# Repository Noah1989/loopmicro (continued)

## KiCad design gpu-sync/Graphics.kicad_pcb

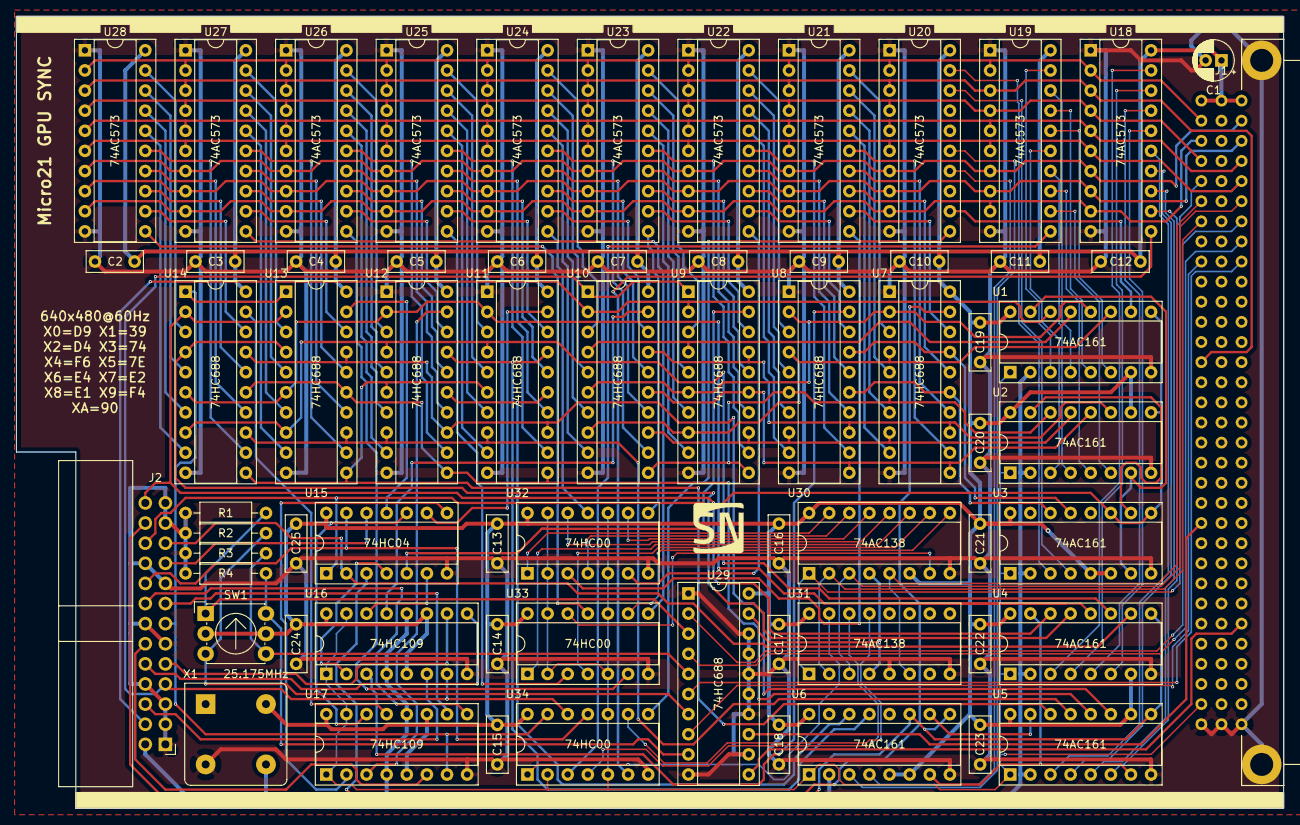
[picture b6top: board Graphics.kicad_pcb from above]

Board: 2 copper layers, 160.0 x 100.0 mm, 67 parts (0 on the bottom side), 183 nets.

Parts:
C1: CP_Small; CP_Radial_D5.0mm_P2.00mm
C2, C3, C4, C5, C6, C7, C8, C9, C10, C11, C12, C13, C14, C15, C16, C17, C18, C19, C20, C21, C22, C23, C24, C25: C_Small; C_Disc_D7.0mm_W2.5mm_P5.00mm
J1: C96ABC; Socket_DIN41612-CaseC1-full-Male-96Pin-3rows
J2: Conn_01x26_Male; IDC-Header_2x13_P2.54mm_Horizontal
R1, R2, R3, R4: 100k; R_Axial_DIN0207_L6.3mm_D2.5mm_P10.16mm_Horizontal
SW1: SW_Coded_SH-7050; Nidec_Copal_SH-7010C
U1, U2, U3, U4, U5, U6: 74AC161; DIP-16_W7.62mm_Socket
U7, U8, U9, U10, U11, U12, U13, U14, U29: 74HC688; DIP-20_W7.62mm_Socket
U15: 74HC04; DIP-14_W7.62mm_Socket
U16, U17: 74HC109; DIP-16_W7.62mm_Socket
U18, U19, U20, U21, U22, U23, U24, U25, U26, U27, U28: 74AC573; DIP-20_W7.62mm_Socket
U30, U31: 74AC138; DIP-16_W7.62mm_Socket
U32, U33, U34: 74HC00; DIP-14_W7.62mm_Socket
X1: 25.175MHz; Oscillator_DIP-8_LargePads

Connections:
/BLANK: J2.18, U15.13, U34.11
/Column Counter/CE: U1.10, U20.12
/Column Counter/D0: U1.3, U19.19
/Column Counter/D1: U1.4, U19.18
/Column Counter/D2: U1.5, U19.17
/Column Counter/D3: U1.6, U19.16
/Column Counter/D4: U2.3, U19.15
/Column Counter/D5: U2.4, U19.14
/Column Counter/D6: U2.5, U19.13
/Column Counter/D7: U2.6, U19.12
/Column Counter/D8: U3.3, U20.19
/Column Counter/D9: U3.4, U20.18
/HBLANK: J2.6, U16.6
/HBLANK Generator/P0: U1.12, U7.2, U8.2, U9.6, U10.6
/HBLANK Generator/P1: U1.11, U7.4, U8.4, U9.8, U10.8
/HBLANK Generator/P2: U2.14, U7.6, U8.6, U9.11, U10.11
/HBLANK Generator/P3: U2.13, U7.8, U8.8, U9.13, U10.13
/HBLANK Generator/P4: U2.12, U7.11, U8.11, U9.15, U10.15
/HBLANK Generator/P5: U2.11, U7.13, U8.13, U9.17, U10.17
/HBLANK Generator/P6: U3.14, U7.15, U8.15
/HBLANK Generator/P7: U3.13, U7.17, U8.17
/HSYNC: J2.9, U16.10
/HSYNC Generator/P0: J2.4, U1.14, U9.2, U10.2
/HSYNC Generator/P1: U1.13, U9.4, U10.4
/PCLK: J2.2, U1.2, U2.2, U3.2, U4.2, U5.2, U6.2, U16.4, U16.12, U17.4, U17.12, X1.5
/Row Counter/D0: U4.3, U18.19
/Row Counter/D1: U4.4, U18.18
/Row Counter/D2: U4.5, U18.17
/Row Counter/D3: U4.6, U18.16
/Row Counter/D4: U5.3, U18.15
/Row Counter/D5: U5.4, U18.14
/Row Counter/D6: U5.5, U18.13
/Row Counter/D7: U5.6, U18.12
/Row Counter/D8: U6.3, U20.15
/Row Counter/D9: U6.4, U20.14
/TCC: J2.21, U4.10, U15.2
/VBLANK: J2.12, U17.6
/VBLANK Generator/P0: U4.12, U11.2, U12.2, U13.6, U14.6
/VBLANK Generator/P1: U4.11, U11.4, U12.4, U13.8, U14.8
/VBLANK Generator/P2: U5.14, U11.6, U12.6, U13.11, U14.11
/VBLANK Generator/P3: U5.13, U11.8, U12.8, U13.13, U14.13
/VBLANK Generator/P4: U5.12, U11.11, U12.11, U13.15, U14.15
/VBLANK Generator/P5: U5.11, U11.13, U12.13, U13.17, U14.17
/VBLANK Generator/P6: U6.14, U11.15, U12.15
/VBLANK Generator/P7: U6.13, U11.17, U12.17
/VSYNC: J2.15, U17.10
/VSYNC Generator/P0: J2.26, U4.14, U13.2, U14.2
/VSYNC Generator/P1: U4.13, U13.4, U14.4
/~BLANK: J2.19, U15.12
/~HBLANK: J2.7, U9.1, U10.1, U16.7, U34.12
/~HSYNC: J2.10, U16.9
/~TCC: J2.22, U1.9, U2.9, U3.9, U3.11, U15.1
/~TCR: J2.24, U4.9, U5.9, U6.9, U6.11
/~VBLANK: J2.13, U13.1, U14.1, U17.7, U34.13
/~VSYNC: J2.16, U17.9
A0: J1.C5, U30.1, U31.1
A1: J1.C7, U30.2, U31.2
A2: J1.A6, U30.3, U31.3
A3: J1.C6, U30.5, U31.6
A4: J1.A7, U29.2
A5: J1.A8, U29.4
A6: J1.A9, U29.6
A7: J1.C9, U29.8
D0: J1.C2, U18.2, U19.2, U20.2, U21.2, U22.2, U23.2, U24.2, U25.2, U26.2, U27.2, U28.2
D1: J1.C14, U18.3, U19.3, U20.3, U21.3, U22.3, U23.3, U24.3, U25.3, U26.3, U27.3, U28.3
D2: J1.C4, U18.4, U19.4, U20.4, U21.4, U22.4, U23.4, U24.4, U25.4, U26.4, U27.4, U28.4
D3: J1.A4, U18.5, U19.5, U20.5, U21.5, U22.5, U23.5, U24.5, U25.5, U26.5, U27.5, U28.5
D4: J1.A5, U18.6, U19.6, U20.6, U21.6, U22.6, U23.6, U24.6, U25.6, U26.6, U27.6, U28.6
D5: J1.A2, U18.7, U19.7, U20.7, U21.7, U22.7, U23.7, U24.7, U25.7, U26.7, U27.7, U28.7
D6: J1.A3, U18.8, U19.8, U20.8, U21.8, U22.8, U23.8, U24.8, U25.8, U26.8, U27.8, U28.8
D7: J1.C3, U18.9, U19.9, U20.9, U21.9, U22.9, U23.9, U24.9, U25.9, U26.9, U27.9, U28.9
GND: C1.2, C2.1, C3.1, C4.1, C5.1, C6.1, C7.1, C8.1, C9.1, C10.1, C11.1, C12.1, C13.1, C14.1, C15.1, C16.1, C17.1, C18.1, C19.1, C20.1, C21.1, C22.1, C23.1, C24.1, C25.1, J1.A32, J1.B32, J1.C32, J2.1, J2.3, J2.5, J2.8, J2.11, J2.14, J2.17, J2.20, J2.23, J2.25, R1.2, R2.2, R3.2, R4.2, U1.8, U2.8, U3.8, U4.8, U5.8, U6.8, U7.1, U7.10, U8.1, U8.10, U9.10, U10.10, U11.1, U11.10, U12.1, U12.10, U13.10, U14.10, U15.7, U16.8, U17.8, U18.1, U18.10, U19.1, U19.10, U20.1, U20.10, U21.1, U21.10, U22.1, U22.10, U23.1, U23.10, U24.1, U24.10, U25.1, U25.10, U26.1, U26.10, U27.1, U27.10, U28.1, U28.10, U29.1, U29.10, U29.12, U29.14, U29.15, U29.16, U29.17, U29.18, U30.8, U31.5, U31.8, U32.7, U33.7, U34.7, X1.4
unnamed: R1.1, SW1.1, U29.3
unnamed: R2.1, SW1.4, U29.7
unnamed: R3.1, SW1.2, U29.5
unnamed: R4.1, SW1.8, U29.9
unnamed: U1.15, U2.7, U3.7
unnamed: U2.15, U3.10
unnamed: U4.15, U5.7, U6.7
unnamed: U5.15, U6.10
unnamed: U10.3, U24.19
unnamed: U10.5, U24.18
unnamed: U10.7, U24.17
unnamed: U10.9, U24.16
unnamed: U10.12, U24.15
unnamed: U10.14, U24.14
unnamed: U10.16, U24.13
unnamed: U10.18, U24.12
unnamed: U10.19, U16.13
unnamed: U11.3, U25.19
unnamed: U11.5, U25.18
unnamed: U11.7, U25.17
unnamed: U11.9, U25.16
unnamed: U11.12, U25.15
unnamed: U11.14, U25.14
unnamed: U11.16, U25.13
unnamed: U11.18, U25.12
unnamed: U11.19, U15.9
unnamed: U12.3, U26.19
unnamed: U12.5, U26.18
unnamed: U12.7, U26.17
unnamed: U12.9, U26.16
unnamed: U12.12, U26.15
unnamed: U12.14, U26.14
unnamed: U12.16, U26.13
unnamed: U12.18, U26.12
unnamed: U12.19, U17.3
unnamed: U13.3, U27.19
unnamed: U13.5, U27.18
unnamed: U13.7, U27.17
unnamed: U13.9, U27.16
unnamed: U13.12, U27.15
unnamed: U13.14, U27.14
unnamed: U13.16, U27.13
unnamed: U13.18, U27.12
unnamed: U13.19, U15.11
unnamed: U14.3, U28.19
unnamed: U14.5, U28.18
unnamed: U14.7, U28.17
unnamed: U14.9, U28.16
unnamed: U14.12, U28.15
unnamed: U14.14, U28.14
unnamed: U14.16, U28.13
unnamed: U14.18, U28.12
unnamed: U14.19, U17.13
unnamed: U7.19, U15.3
unnamed: U15.4, U16.2
unnamed: U9.19, U15.5
unnamed: U15.6, U16.14
unnamed: U15.8, U17.2
unnamed: U15.10, U17.14
unnamed: U8.19, U16.3
unnamed: U18.11, U34.6
unnamed: U19.11, U34.3
unnamed: U20.11, U34.8
unnamed: U21.11, U32.3
unnamed: U7.18, U21.12
unnamed: U7.16, U21.13
unnamed: U7.14, U21.14
unnamed: U7.12, U21.15
unnamed: U7.9, U21.16
unnamed: U7.7, U21.17
unnamed: U7.5, U21.18
unnamed: U7.3, U21.19
unnamed: U22.11, U32.6
unnamed: U8.18, U22.12
unnamed: U8.16, U22.13
unnamed: U8.14, U22.14
unnamed: U8.12, U22.15
unnamed: U8.9, U22.16
unnamed: U8.7, U22.17
unnamed: U8.5, U22.18
unnamed: U8.3, U22.19
unnamed: U23.11, U32.8
unnamed: U9.18, U23.12
unnamed: U9.16, U23.13
unnamed: U9.14, U23.14
unnamed: U9.12, U23.15
unnamed: U9.9, U23.16
unnamed: U9.7, U23.17
unnamed: U9.5, U23.18
unnamed: U9.3, U23.19
unnamed: U24.11, U32.11
unnamed: U25.11, U33.3
unnamed: U26.11, U33.6
unnamed: U27.11, U33.8
unnamed: U28.11, U33.11
unnamed: U29.19, U30.4, U31.4
VCC: C1.1, C2.2, C3.2, C4.2, C5.2, C6.2, C7.2, C8.2, C9.2, C10.2, C11.2, C12.2, C13.2, C14.2, C15.2, C16.2, C17.2, C18.2, C19.2, C20.2, C21.2, C22.2, C23.2, C24.2, C25.2, J1.A1, J1.B1, J1.C1, SW1.C, U1.7, U1.16, U2.10, U2.16, U3.5, U3.6, U3.16, U4.7, U4.16, U5.10, U5.16, U6.5, U6.6, U6.16, U7.20, U8.20, U9.20, U10.20, U11.20, U12.20, U13.20, U14.20, U15.14, U16.5, U16.11, U16.16, U17.5, U17.11, U17.16, U18.20, U19.20, U20.20, U21.20, U22.20, U23.20, U24.20, U25.20, U26.20, U27.20, U28.20, U29.20, U30.6, U30.16, U31.16, U32.14, U33.14, U34.14, X1.8
~CS0: U30.15, U32.1
~CS1: U30.14, U32.4
~CS2: U30.13, U32.9
~CS3: U30.12, U32.12
~CS4: U30.11, U33.1
~CS5: U30.10, U33.4
~CS6: U30.9, U33.9
~CS7: U30.7, U33.12
~CS8: U31.15, U34.1
~CS9: U31.14, U34.4
~CS10: U31.13, U34.9
~IORQ: J1.A27, U29.11
~RESET: J1.C31, U1.1, U2.1, U3.1, U4.1, U5.1, U6.1, U16.1, U16.15, U17.1, U17.15, U32.2, U32.5, U32.10, U32.13, U33.2, U33.5, U33.10, U33.13, U34.2, U34.5, U34.10
~WR: J1.C22, U29.13

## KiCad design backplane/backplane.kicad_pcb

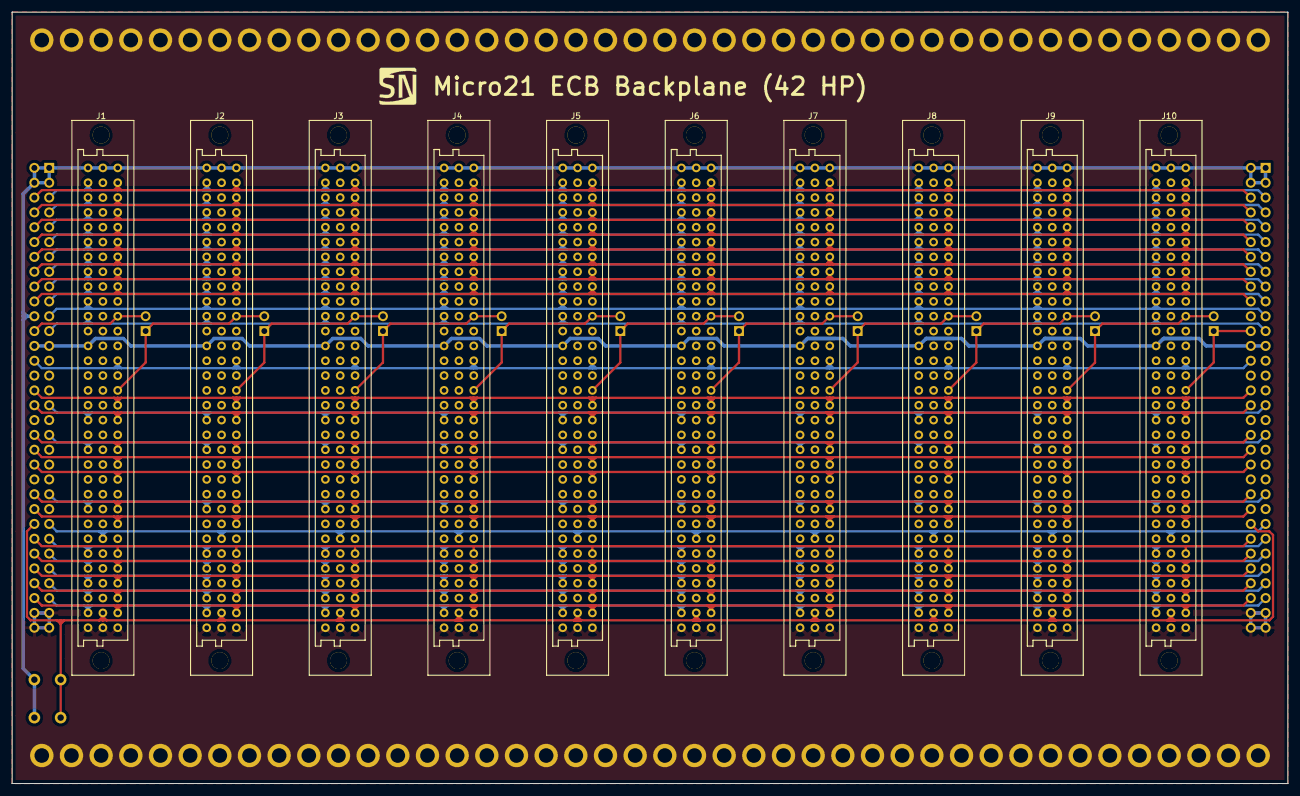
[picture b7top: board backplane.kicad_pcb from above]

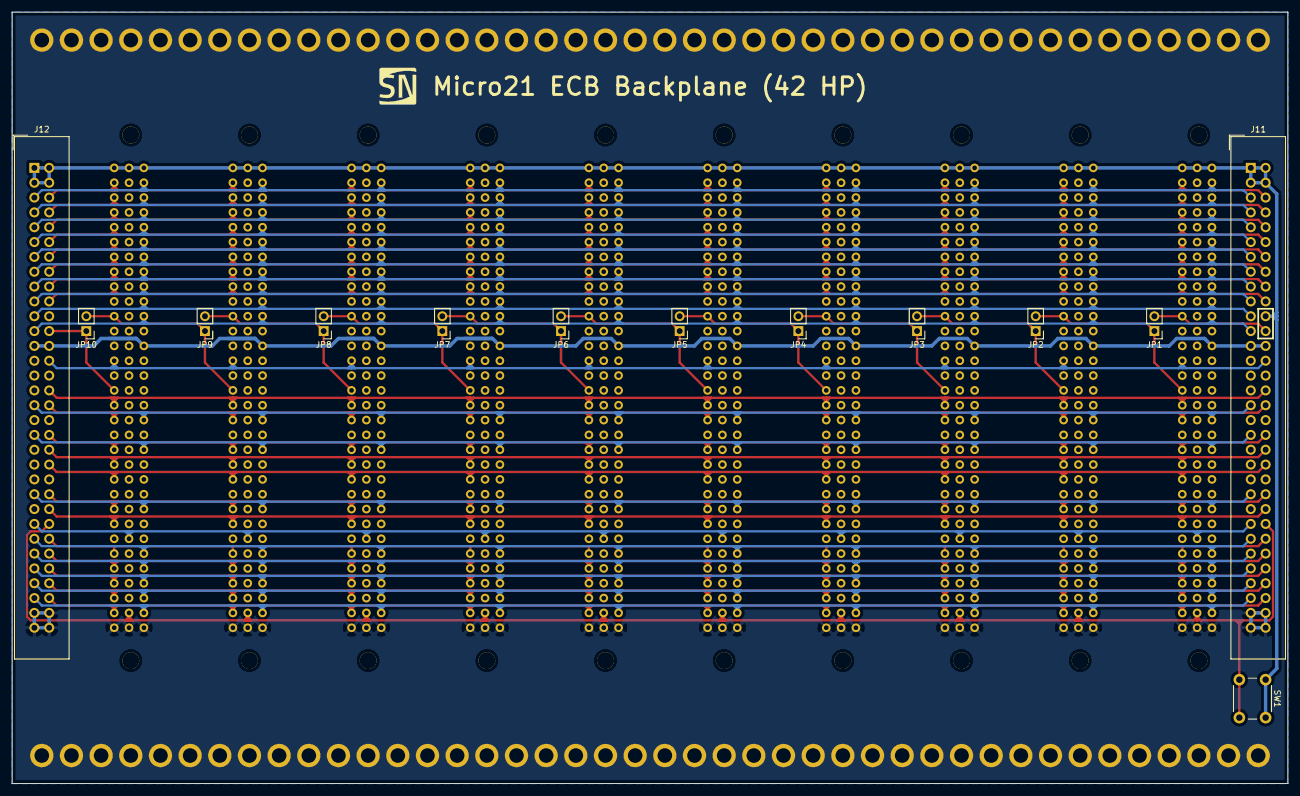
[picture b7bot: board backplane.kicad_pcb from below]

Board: 2 copper layers, 218.4 x 132.1 mm, 23 parts (13 on the bottom side), 55 nets.

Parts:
J1, J2, J3, J4, J5, J6, J7, J8, J9, J10: C96ABC; Socket_DIN41612-CaseC1-full-Female-96Pin-3rows
J11, J12: Conn_02x32_Odd_Even; IDC-Header_2x32_P2.54mm_Vertical
JP1, JP2, JP3, JP4, JP5, JP6, JP7, JP8, JP9, JP10: Jumper; PinHeader_1x02_P2.54mm_Vertical
SW1: SW_Push; SW_PUSH_6mm_H7.3mm

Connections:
+12V: J1.A13, J2.A13, J3.A13, J4.A13, J5.A13, J6.A13, J7.A13, J8.A13, J9.A13, J10.A13, J11.25, J11.26, J12.25, J12.26
+BATT: J1.A24, J2.A24, J3.A24, J4.A24, J5.A24, J6.A24, J7.A24, J8.A24, J9.A24, J10.A24, J11.45, J12.45
A0: J1.C5, J2.C5, J3.C5, J4.C5, J5.C5, J6.C5, J7.C5, J8.C5, J9.C5, J10.C5, J11.12, J12.12
A1: J1.C7, J2.C7, J3.C7, J4.C7, J5.C7, J6.C7, J7.C7, J8.C7, J9.C7, J10.C7, J11.16, J12.16
A2: J1.A6, J2.A6, J3.A6, J4.A6, J5.A6, J6.A6, J7.A6, J8.A6, J9.A6, J10.A6, J11.13, J12.13
A3: J1.C6, J2.C6, J3.C6, J4.C6, J5.C6, J6.C6, J7.C6, J8.C6, J9.C6, J10.C6, J11.14, J12.14
A4: J1.A7, J2.A7, J3.A7, J4.A7, J5.A7, J6.A7, J7.A7, J8.A7, J9.A7, J10.A7, J11.15, J12.15
A5: J1.A8, J2.A8, J3.A8, J4.A8, J5.A8, J6.A8, J7.A8, J8.A8, J9.A8, J10.A8, J11.17, J12.17
A6: J1.A9, J2.A9, J3.A9, J4.A9, J5.A9, J6.A9, J7.A9, J8.A9, J9.A9, J10.A9, J11.19, J12.19
A7: J1.C9, J2.C9, J3.C9, J4.C9, J5.C9, J6.C9, J7.C9, J8.C9, J9.C9, J10.C9, J11.20, J12.20
A8: J1.C8, J2.C8, J3.C8, J4.C8, J5.C8, J6.C8, J7.C8, J8.C8, J9.C8, J10.C8, J11.18, J12.18
A9: J1.A30, J2.A30, J3.A30, J4.A30, J5.A30, J6.A30, J7.A30, J8.A30, J9.A30, J10.A30, J11.57, J12.57
A10: J1.C18, J2.C18, J3.C18, J4.C18, J5.C18, J6.C18, J7.C18, J8.C18, J9.C18, J10.C18, J11.34, J12.34
A11: J1.C17, J2.C17, J3.C17, J4.C17, J5.C17, J6.C17, J7.C17, J8.C17, J9.C17, J10.C17, J11.32, J12.32
A12: J1.C27, J2.C27, J3.C27, J4.C27, J5.C27, J6.C27, J7.C27, J8.C27, J9.C27, J10.C27, J11.52, J12.52
A13: J1.A29, J2.A29, J3.A29, J4.A29, J5.A29, J6.A29, J7.A29, J8.A29, J9.A29, J10.A29, J11.55, J12.55
A14: J1.A18, J2.A18, J3.A18, J4.A18, J5.A18, J6.A18, J7.A18, J8.A18, J9.A18, J10.A18, J11.33, J12.33
A15: J1.C28, J2.C28, J3.C28, J4.C28, J5.C28, J6.C28, J7.C28, J8.C28, J9.C28, J10.C28, J11.54, J12.54
CLK: J1.C29, J2.C29, J3.C29, J4.C29, J5.C29, J6.C29, J7.C29, J8.C29, J9.C29, J10.C29, J11.56, J12.56
D0: J1.C2, J2.C2, J3.C2, J4.C2, J5.C2, J6.C2, J7.C2, J8.C2, J9.C2, J10.C2, J11.6, J12.6
D1: J1.C14, J2.C14, J3.C14, J4.C14, J5.C14, J6.C14, J7.C14, J8.C14, J9.C14, J10.C14, J11.28, J12.28
D2: J1.C4, J2.C4, J3.C4, J4.C4, J5.C4, J6.C4, J7.C4, J8.C4, J9.C4, J10.C4, J11.10, J12.10
D3: J1.A4, J2.A4, J3.A4, J4.A4, J5.A4, J6.A4, J7.A4, J8.A4, J9.A4, J10.A4, J11.9, J12.9
D4: J1.A5, J2.A5, J3.A5, J4.A5, J5.A5, J6.A5, J7.A5, J8.A5, J9.A5, J10.A5, J11.11, J12.11
D5: J1.A2, J2.A2, J3.A2, J4.A2, J5.A2, J6.A2, J7.A2, J8.A2, J9.A2, J10.A2, J11.5, J12.5
D6: J1.A3, J2.A3, J3.A3, J4.A3, J5.A3, J6.A3, J7.A3, J8.A3, J9.A3, J10.A3, J11.7, J12.7
D7: J1.C3, J2.C3, J3.C3, J4.C3, J5.C3, J6.C3, J7.C3, J8.C3, J9.C3, J10.C3, J11.8, J12.8
GND: J1.A32, J1.B32, J1.C32, J2.A32, J2.B32, J2.C32, J3.A32, J3.B32, J3.C32, J4.A32, J4.B32, J4.C32, J5.A32, J5.B32, J5.C32, J6.A32, J6.B32, J6.C32, J7.A32, J7.B32, J7.C32, J8.A32, J8.B32, J8.C32, J9.A32, J9.B32, J9.C32, J10.A32, J10.B32, J10.C32, J11.61, J11.62, J11.63, J11.64, J12.61, J12.62, J12.63, J12.64
unnamed: J1.C11, J11.24, JP1.2
unnamed: J1.C16, J2.C11, JP1.1, JP2.2
unnamed: J2.C16, J3.C11, JP2.1, JP3.2
unnamed: J3.C16, J4.C11, JP3.1, JP4.2
unnamed: J4.C16, J5.C11, JP4.1, JP5.2
unnamed: J5.C16, J6.C11, JP5.1, JP6.2
unnamed: J6.C16, J7.C11, JP6.1, JP7.2
unnamed: J7.C16, J8.C11, JP7.1, JP8.2
unnamed: J8.C16, J9.C11, JP8.1, JP9.2
unnamed: J9.C16, J10.C11, JP9.1, JP10.2
unnamed: J10.C16, J12.24, JP10.1
RESB: J1.B31, J2.B31, J3.B31, J4.B31, J5.B31, J6.B31, J7.B31, J8.B31, J9.B31, J10.B31, J11.50, J12.50, SW1.2
VCC: J1.A1, J1.B1, J1.C1, J2.A1, J2.B1, J2.C1, J3.A1, J3.B1, J3.C1, J4.A1, J4.B1, J4.C1, J5.A1, J5.B1, J5.C1, J6.A1, J6.B1, J6.C1, J7.A1, J7.B1, J7.C1, J8.A1, J8.B1, J8.C1, J9.A1, J9.B1, J9.C1, J10.A1, J10.B1, J10.C1, J11.1, J11.2, J11.3, J11.4, J11.22, J12.1, J12.2, J12.3, J12.4, SW1.1
~BUSAK: J1.A31, J2.A31, J3.A31, J4.A31, J5.A31, J6.A31, J7.A31, J8.A31, J9.A31, J10.A31, J11.59, J12.59
~BUSRQ: J1.A11, J2.A11, J3.A11, J4.A11, J5.A11, J6.A11, J7.A11, J8.A11, J9.A11, J10.A11, J11.23, J12.23
~HALT: J1.C25, J2.C25, J3.C25, J4.C25, J5.C25, J6.C25, J7.C25, J8.C25, J9.C25, J10.C25, J11.48, J12.48
~INT: J1.C21, J2.C21, J3.C21, J4.C21, J5.C21, J6.C21, J7.C21, J8.C21, J9.C21, J10.C21, J11.40, J12.40
~IORQ: J1.A27, J2.A27, J3.A27, J4.A27, J5.A27, J6.A27, J7.A27, J8.A27, J9.A27, J10.A27, J11.51, J12.51
~M1: J1.A20, J2.A20, J3.A20, J4.A20, J5.A20, J6.A20, J7.A20, J8.A20, J9.A20, J10.A20, J11.37, J12.37
~MREQ: J1.C30, J2.C30, J3.C30, J4.C30, J5.C30, J6.C30, J7.C30, J8.C30, J9.C30, J10.C30, J11.58, J12.58
~NMI: J1.C20, J2.C20, J3.C20, J4.C20, J5.C20, J6.C20, J7.C20, J8.C20, J9.C20, J10.C20, J11.38, J12.38
~RD: J1.C24, J2.C24, J3.C24, J4.C24, J5.C24, J6.C24, J7.C24, J8.C24, J9.C24, J10.C24, J11.46, J12.46
~RESET: J1.C31, J2.C31, J3.C31, J4.C31, J5.C31, J6.C31, J7.C31, J8.C31, J9.C31, J10.C31, J11.60, J12.60
~RFSH: J1.A28, J2.A28, J3.A28, J4.A28, J5.A28, J6.A28, J7.A28, J8.A28, J9.A28, J10.A28, J11.53, J12.53
~ROB: J1.B26, J2.B26, J3.B26, J4.B26, J5.B26, J6.B26, J7.B26, J8.B26, J9.B26, J10.B26, J11.49, J12.49
~WAIT: J1.A10, J2.A10, J3.A10, J4.A10, J5.A10, J6.A10, J7.A10, J8.A10, J9.A10, J10.A10, J11.21, J12.21
~WR: J1.C22, J2.C22, J3.C22, J4.C22, J5.C22, J6.C22, J7.C22, J8.C22, J9.C22, J10.C22, J11.42, J12.42
